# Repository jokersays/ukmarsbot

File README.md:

# update CW2025
## wall sensor
- LED (sichtbares Licht): TCLR5800 https://eu.mouser.com/ProductDetail/Vishay-Semiconductors/TLCR5800?qs=mUuSc%2Fu%252BFEmjc7YwQS0o5A%3D%3D&srsltid=AfmBOopzCn7n3C-wtkQbLPWO1j8fxE9Hj8DcGLDCGrcggpLkpXWju-RC
- Phototransistor: BPW96B https://www.mouser.de/ProductDetail/Vishay-Semiconductors/BPW96B?qs=%2Fjqivxn91cdilznm00Ncpg%3D%3D&utm_id=10065984414&utm_source=google&utm_medium=cpc&utm_marketing_tactic=emeacorp&gad_source=5&gad_campaignid=10065984414&gclid=EAIaIQobChMIq9jEloT5jgMVpy0GAB1_qAhfEAAYAiAAEgKWzvD_BwE

## motor
- N20 Gear Motor mit Encoder, 6V, 20:1 / ~1000 RPM (oder 750 RPM) AliExpress?

## capacitor
- 470uF 10V 6.3mm, <12mm h, radial 2.5
- 330uF 10V radial 2.5
--> mouser

# ukmarsbot

__A simple beginner's multi purpose robot platform__

Using inexpensive, readily available materials, components and techniques, the UK Micromouse and Robotics Society (UKMARS) has created a basic robot design that can be used in a variety of common contests such as line following, wall following, drag race and mini-sumo.

## Contents

This repository is all about the robot itself. Software is provided in other UKMARS repositories. 

 - Software examples https://github.com/ukmars/ukmarsbot-examples
 - Full maze solving software: https://github.com/ukmars/ukmarsbot-mazerunner

The repository has a number of sections:

 - [__docs__](docs) contains miscellaneous documentation and datasheets. In there are some notes about design decisions and constraints, processor choice and configuration, and a bit about sensors.
 - [__ecad__](ecad) contains the design files for the various electronic modules that make up the robot. The original development was done with Eagle Version 7 since it was the last 'free' version of Eagle. More recent versions are likely to be developed in KiCad since it is free, unconstrained and multiplatform. You are only likely to need to look in here f you want to modify existing modules or create your own. Either Eagle or KiCad can be used for new development.
 - [__hardware__](hardware) holds subsections for the major parts that make up the robot - the main PCB and all the sensor boards. This is where you find the outputs from the ECAD tools. You don't need to know anything about Eagle or KiCad to use these outputs. For each module you should find a set of gerbers in a zip file so that you can easily order boards from your favourite supplier. Also present should be the schematics in PDF form, images of the finished boards and a parts list (BOM) to help you populate the board and select components. Note that many component choices are up to the builder and there are a number of options possible. Some or all of these elements may be missing or incomplete. Let us know of any shortcomings by raising [a new issue on github](https://github.com/ukmars/ukmarsbot/issues).
 - [__mechanical__](mechanical) contains a number of mechanical CAD files. These are most likely to be STL or STEP files  and are for components that can be 3D printed tohelp you make your robot. For example you will find motor mounts and brackets here.
 - [__renders__](renders) is a place where we keep generated images of the robot and some components. You can get an idea of how your finished robot may look as well as see some of the prototypes that led to the current design.
 - [__resources__](resources) is really a dump for stuff that does not fit in with the rest. At the tie of writing this is just a section about data logging.

## The Processor
Processor power is provided by the Arduino Nano board because it is very cheap and widely available. There is a huge range of sample code available for almost any purpose and support is easily found online. The Arduino software can be installed on any computer and is free.

A proposed pin usage for an Arduino Nano controller can be found in the [docs](docs) folder.

because the Arduino Nano is a popular processor module, there are many compatible or near-compatible alternative boards available. The processor module socket makes it possible to use some of these directly with only small modifications or, with a little more work you might fit almost any processor. Variants have already been built with STM32 processors and even a Raspberry Pi pico and Zero board.

## Bluetooth

Some alternative processors in the Arduino range already have Bluetooth and WiFi built in. If you stick with simpler options - like the Arduino Nano - there is a connector provided for you to attach one of the common HC05 or HC06 Bluetooth modules directly to the board to make a wireless serial connection. Circuitry on the board (V1.1 and later) allowyou to leave the BT module connected during programming. You can then use any serial terminal, including the Arduino terminal, to communicate with the robot over Bluetooth.

### Coding
The easiest language for starting coding with the Arduino, and the method most people use, is to create a  "Sketch" using the Arduino Integrated Development Environment (IDE). A "Sketch" comprises functions written with C/C++ statements and the Arduino IDE takes care of turning the sketch into a complete program and uploading it to the Arduino board. It can run on any of the major platforms: Windows, Mac and Linux enabling Sketch programs for the Arduino to be readily developed on any PC. The Arduino project has lots of examples and help available for creating code, as well as libraries of functions to carry out specific tasks.

The Arduino IDE requires software to be downloaded and installed on the development PC as well as drivers to enable the developed code to be downloaded using the USB cable onto the Arduino board. All of this software and drivers are free and easy to install as long as you have software install permissions on the PC.

There is also a recently introduced web based development environment, but as yet this does not support all Arduino models and platforms. and still requires various plug ins to be installed on the development PC to use it. Find out more here: https://www.arduino.cc/en/software

A very popular alternative to the Arduino IDE is PlatformIO which can be fully integrated into the excellent VSCode editor. A 'getting started' guide for this environment is available here: https://docs.platformio.org/en/latest/integration/ide/vscode.html

Alternative software environments are available and are identified at the end of this document.

### Hardware

The robot hardware is constrained by the various contest events to be within certain dimensional limits. That means that the basic chassis will be smaller than 100mm x 100mm although add-on sensors for individual events will increase the size. The robot is designed to be multipurpose so there is a core hardware setup that provides for a basic wheelchair drive of two motors, encoder feedback for individual motor speed and a minimal interface for user interaction. Components will be modular so that substitutions are easy and to provide the greatest flexibility. Builders are free to make whatever modifications suit their purpose. For example, larger or smaller motors and wheels may be used and a variety of sensor options are possible.

### Power Supply

For most purposes, the power supply for the robot will need to be compact, readily available and easy to recharge. Non rechargeable batteries are not economically viable for robot experiment and are, in any case, less environmentally friendly. Safety is a concern and so Lithium Polymer cells are only recommended when part of a regulated and protected pack. Perhaps the most common small battery is the rechargeable PP3 sized pack running at 8.4 Volts or 9 Volts. Rechargeable cells and their chargers can be purchased at supermarkets and online suppliers. More confident, or adventurous builders may install whatever power supply suits them.

### Motors

While there is endless variety in small DC electric motors, the N20-based gearmotors are excellent value for money and can be purchased in a huge range of performance characteristics. An example can be found here: [Pimoroni 20:1 gearmotor](https://shop.pimoroni.com/products/micro-metal-gearmotor-extended-back-shaft?variant=32587847050). The common dimensions make it easy to swap motors without changing the mechanical design of the robot. Versions are available with built-in encoders allowing for more accurate control of speed and greater precision in movement of the robot. Normally these would be used in any robot. The drivers for these motors are available on small circuit board modules that can easily be connected with the Arduino Nano.

### Materials

It will be possible to build the robot using parts that are commercially readily available and specialist materials will not be required. Access to basic hand tools and soldering equipment will be necessary.

It is likely that some builders will have some access to a 3D printer or a laser cutter or both and the open design of the robot with upgrade paths will allow advanced builders to utilize these tools to create higher performing robots.

### Software

The two software repositories mentioned above provide a fairly complete set of examples and code for almost every aspect of programming for the UKMARSBOT platform. Many of the techniques and examples will also be directly applicable to other mobile robot projects.

If the Arduino IDE is not for you, then there are other programming choices to suit you. (__None of these have been tried by UKMARS__)

* FlashForth http://flashforth.com/ is a Forth stamp system implemented on the Microchip 8-bit PIC18F and 16-bit PIC24, 30, 33 and the Atmel Atmega microcontroller families. See also https://playground.arduino.cc/CommonTopics/ForthOnArduino/ for other options relating to Forth.

* For Basic users there appear to be fewer options. One of these is Great Cow basic http://gcbasic.sourceforge.net/Typesetter/index.php/Home. _"The  Great Cow BASIC suite is robust and fully functional compiler and assembler.   Using Great Cow BASIC is the fastest method to program a Microchip PIC or Atmel AVR 8-bit microcontroller for those just starting and the professional user."_  The host software is cross platform and there is a graphical editor as well as a more traditional IDE.

* Some users may prefer a visual programming environment similar to Scratch. Several of these are available and more information may be found here [Sparkfun Alternative Arduino Interfaces](https://learn.sparkfun.com/tutorials/alternative-arduino-interfaces/all).

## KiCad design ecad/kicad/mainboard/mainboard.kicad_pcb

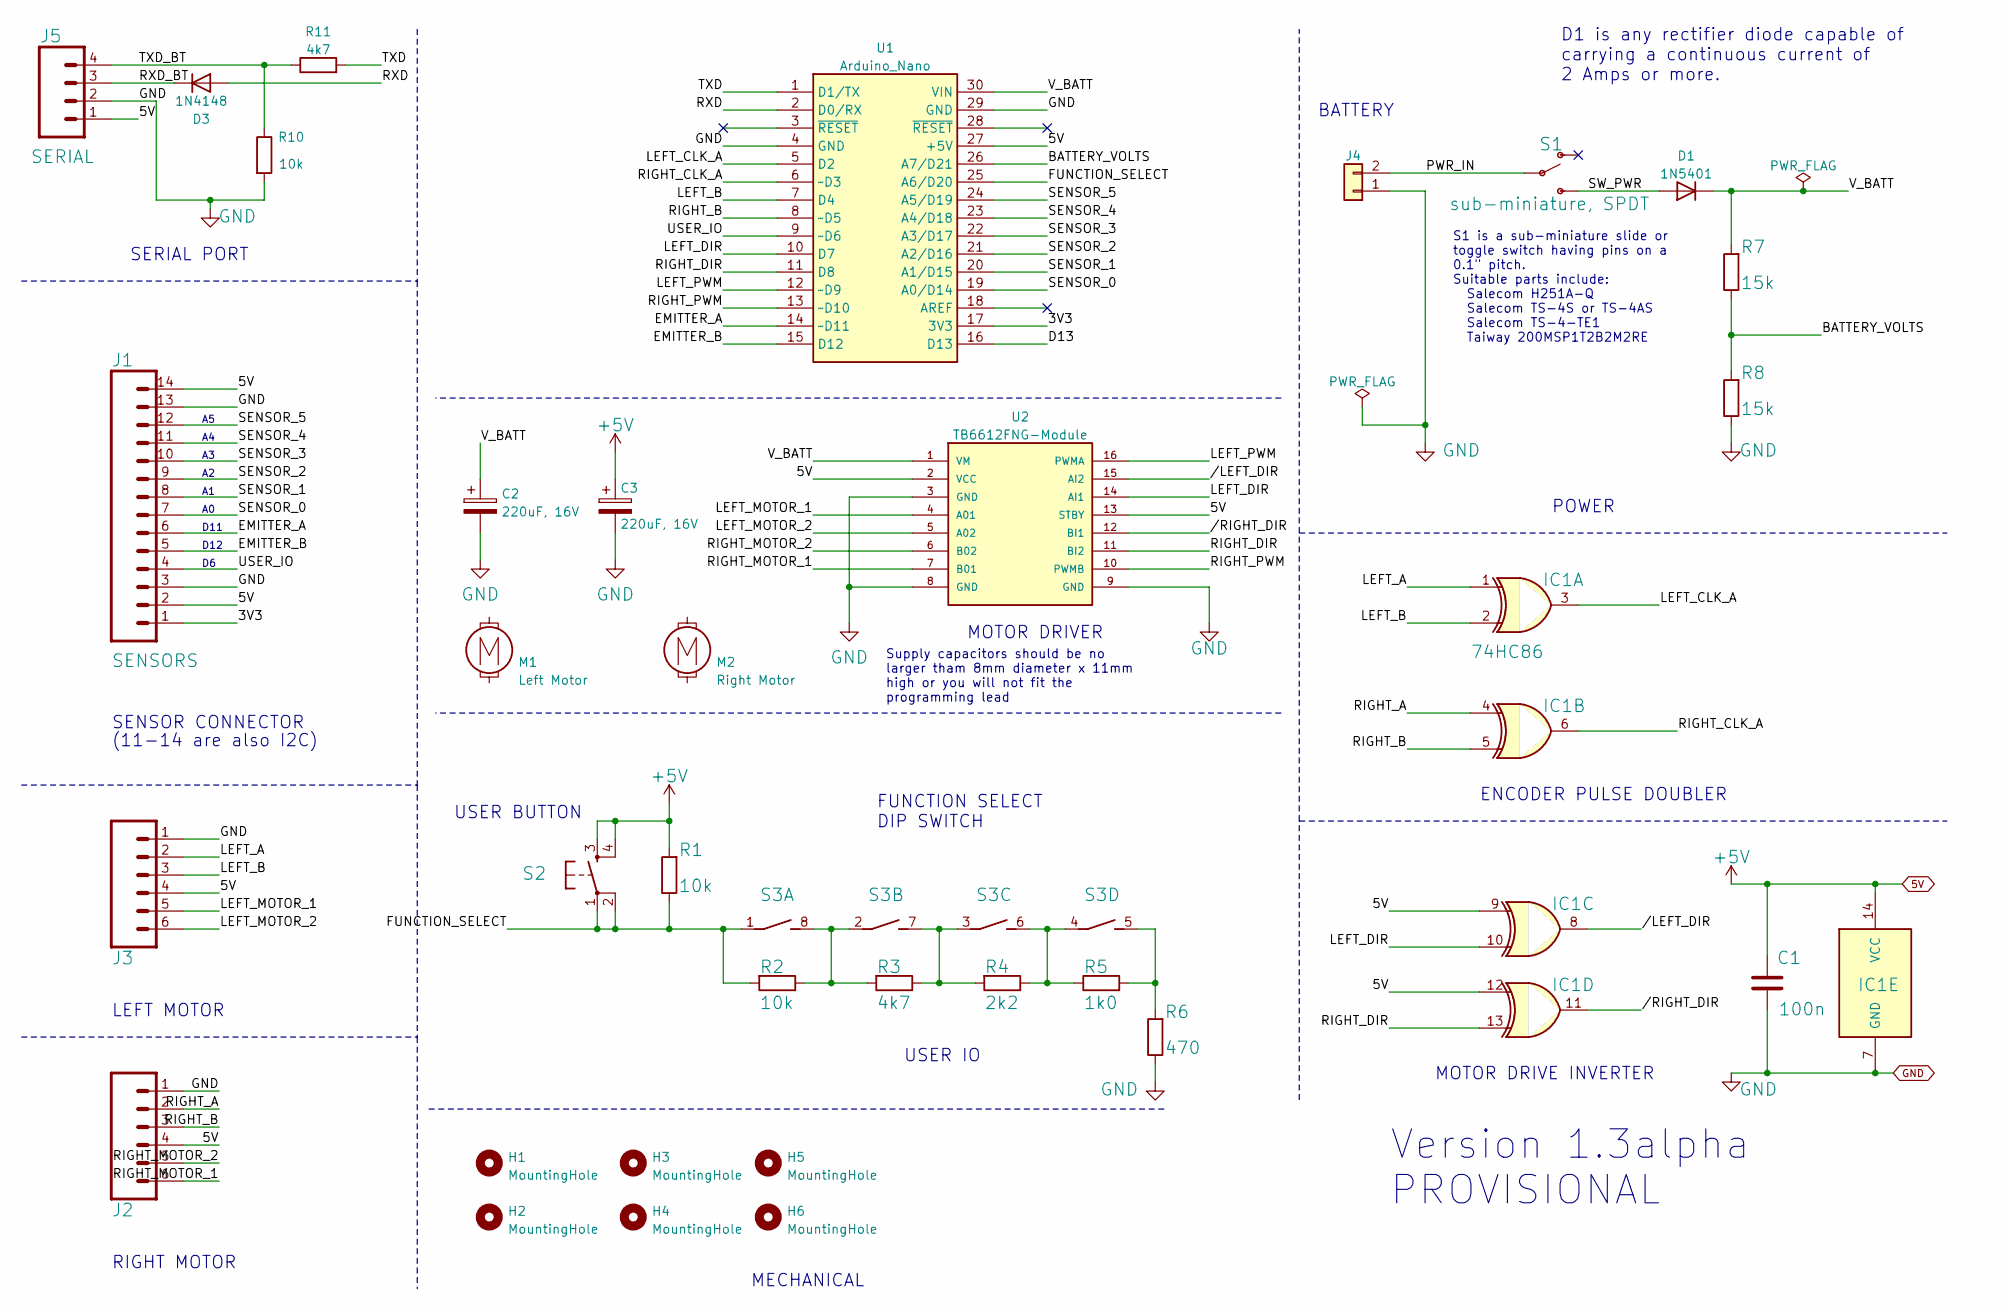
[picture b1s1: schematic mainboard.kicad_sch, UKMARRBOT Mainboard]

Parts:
C1: 100n; C_Rect_L4.6mm_W2.0mm_P2.50mm_MKS02_FKP02
C2, C3: 220uF, 16V; CP_Elec_8x10
D1: 1N5401; D_DO-201AD_P15.24mm_Horizontal
D3: 1N4148; D_DO-35_SOD27_P7.62mm_Horizontal
H1, H2, H3, H4, H5, H6: MountingHole; MountingHole_3.2mm_M3_clearance
IC1: 74HC86; DIP-14_W7.62mm_LongPads
J1: SENSORS; 1X14_LOCK_LONGPADS
J2, J3: CONN_06SILK_FEMALE_PTH; 1X06_LOCK_LONGPADS
J4: POWER; Molex_KK-254_AE-6410-02A_1x02_P2.54mm_Vertical
J5: SERIAL; 1X04_LOCK_LONGPADS
M1: Left Motor; MINI-METAL-GEARMOTOR-WITH-BRACKET
M2: Right Motor; MINI-METAL-GEARMOTOR-WITH-BRACKET
R1, R2, R10: 10k; R_Axial_DIN0207_L6.3mm_D2.5mm_P7.62mm_BIGPAD
R3, R11: 4k7; R_Axial_DIN0207_L6.3mm_D2.5mm_P7.62mm_BIGPAD
R4: 2k2; R_Axial_DIN0207_L6.3mm_D2.5mm_P7.62mm_BIGPAD
R5: 1k0; R_Axial_DIN0207_L6.3mm_D2.5mm_P7.62mm_BIGPAD
R6: 470; R_Axial_DIN0207_L6.3mm_D2.5mm_P7.62mm_BIGPAD
R7, R8: 15k; R_Axial_DIN0207_L6.3mm_D2.5mm_P7.62mm_BIGPAD
S1: sub-miniature, SPDT; SW_MINI-SPDT-SW
S2: BUTTON; TACTILE_SWITCH_PTH_6.0MM
S3: DIP-SW; SW_DIP_SPSTx04_Slide_6.7x11.72mm_W7.62mm_P2.54mm_LowProfile
U1: Arduino_Nano
U2: TB6612FNG-Module; TB6612FNG-module; PARTREV 11-13-17

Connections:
5V: C1.1, C3.1, IC1.9, IC1.12, IC1.14 (VCC), J1.2, J1.14, J2.4, J3.4, J5.1, R1.2, S2.3, S2.4, U1.27 (+5V), U2.2 (VCC), U2.13 (STBY)
/3V3: J1.1, U1.17 (3V3)
/BATTERY_VOLTS: R7.1, R8.2, U1.26 (A7/D21)
/D13: U1.16 (D13)
/EMITTER_A: J1.6, U1.14 (~D11)
/EMITTER_B: J1.5, U1.15 (D12)
/FUNCTION_SELECT: R1.1, R2.2, S2.1, S2.2, S3.1, U1.25 (A6/D20)
/LEFT_A: IC1.1, J3.2
/LEFT_B: IC1.2, J3.3, U1.7 (D4)
/LEFT_CLK_A: IC1.3, U1.5 (D2)
/LEFT_DIR: IC1.10, U1.10 (D7), U2.14 (AI1)
/LEFT_MOTOR_1: J3.5, U2.4 (A01)
/LEFT_MOTOR_2: J3.6, U2.5 (A02)
/LEFT_PWM: U1.12 (~D9), U2.16 (PWMA)
/PWR_IN: J4.2, S1.2
/RIGHT_A: IC1.4, J2.2
/RIGHT_B: IC1.5, J2.3, U1.8 (~D5)
/RIGHT_CLK_A: IC1.6, U1.6 (~D3)
/RIGHT_DIR: IC1.13, U1.11 (D8), U2.11 (BI2)
/RIGHT_MOTOR_1: J2.6, U2.7 (B01)
/RIGHT_MOTOR_2: J2.5, U2.6 (B02)
/RIGHT_PWM: U1.13 (~D10), U2.10 (PWMB)
/RXD: D3.2 (A), U1.2 (D0/RX)
/RXD_BT: D3.1 (K), J5.3
/SENSOR_0: J1.7, U1.19 (A0/D14)
/SENSOR_1: J1.8, U1.20 (A1/D15)
/SENSOR_2: J1.9, U1.21 (A2/D16)
/SENSOR_3: J1.10, U1.22 (A3/D17)
/SENSOR_4: J1.11, U1.23 (A4/D18)
/SENSOR_5: J1.12, U1.24 (A5/D19)
/SW_PWR: D1.2 (A), S1.3 (S)
/TXD: R11.2, U1.1 (D1/TX)
/TXD_BT: J5.4, R10.1, R11.1
/USER_IO: J1.4, U1.9 (~D6)
/V_BATT: C2.1, D1.1 (K), R7.2, U1.30 (VIN), U2.1 (VM)
//LEFT_DIR: IC1.8, U2.15 (AI2)
//RIGHT_DIR: IC1.11, U2.12 (BI1)
GND: C1.2, C2.2, C3.2, IC1.7 (GND), J1.3, J1.13, J2.1, J3.1, J4.1, J5.2, R6.1, R8.1, R10.2, U1.4 (GND), U1.29 (GND), U2.3 (GND), U2.8 (GND), U2.9 (GND)
unnamed: R2.1, R3.2, S3.2 (1), S3.8 (2)
unnamed: R3.1, R4.2, S3.3 (1), S3.7 (2)
unnamed: R4.1, R5.1, S3.4 (1), S3.6 (2)
unnamed: R5.2, R6.2, S3.5 (2)

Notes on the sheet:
MOTOR DRIVER
D1 is any rectifier diode capable of carrying a continuous current of 2 Amps or more.
USER IO
POWER
MOTOR DRIVE INVERTER
FUNCTION SELECT DIP SWITCH
Supply capacitors should be no larger tham 8mm diameter x 11mm high or you will not fit the programming lead
S1 is a sub-miniature slide or toggle switch having pins on a 0.1" pitch. Suitable parts include: Salecom H251A-Q Salecom TS-4S or TS-4AS Salecom TS-4-TE1 Taiway 200MSP1T2B2M2RE
RIGHT MOTOR
SERIAL PORT
SENSOR CONNECTOR
BATTERY
MECHANICAL
ENCODER PULSE DOUBLER
USER BUTTON
D11
Version 1.3alpha PROVISIONAL
LEFT MOTOR
(11-14 are also I2C)
D12

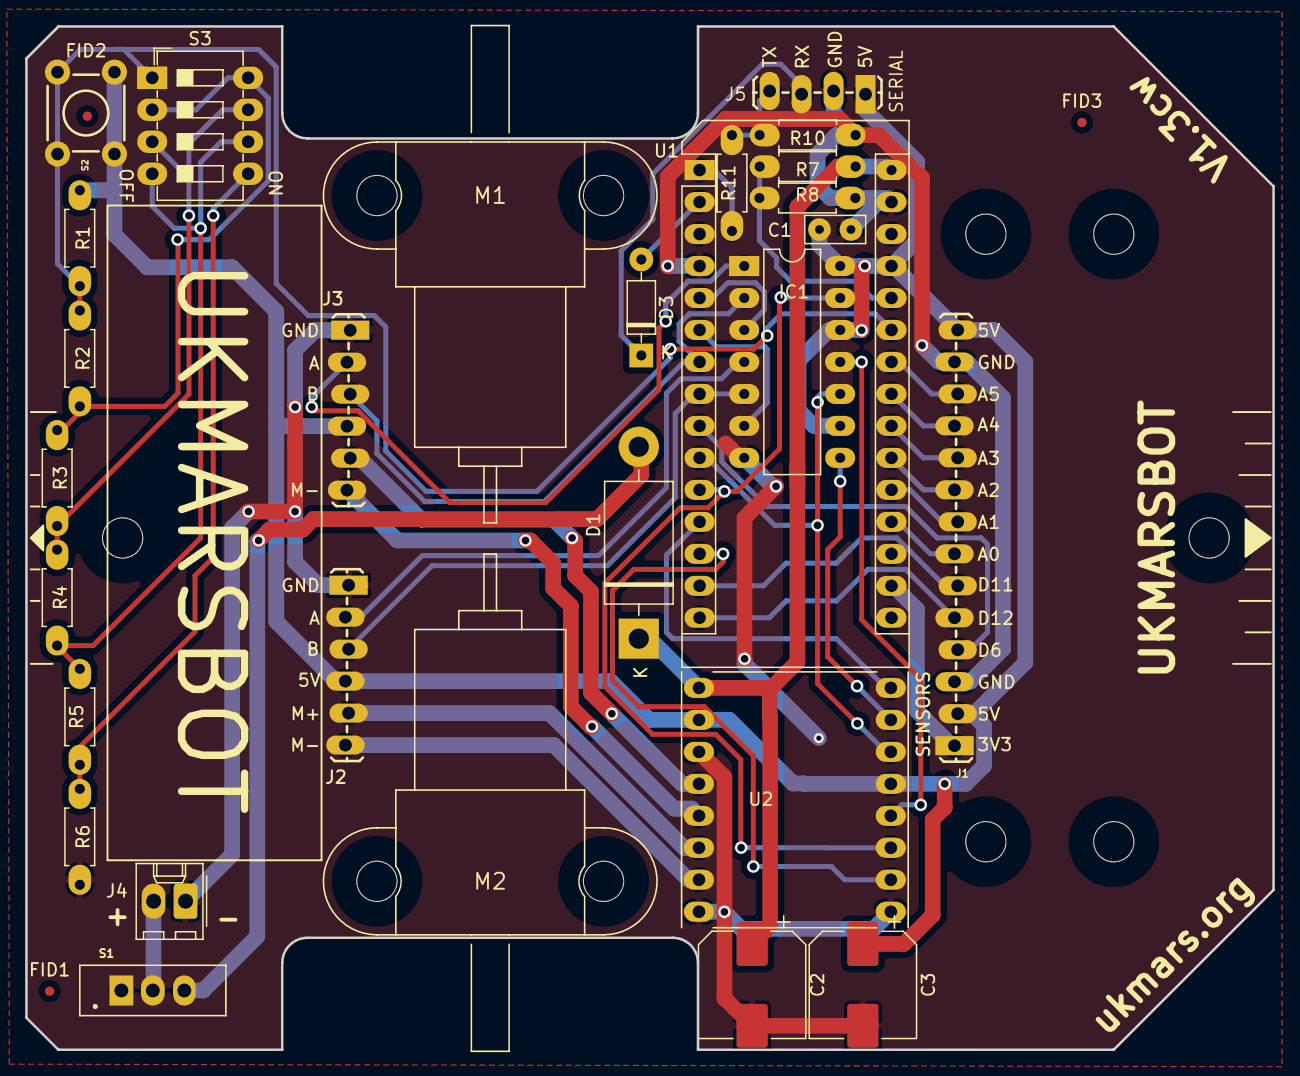
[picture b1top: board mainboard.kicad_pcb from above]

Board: 2 copper layers, 99.1 x 81.3 mm, 37 parts (0 on the bottom side), 41 nets.

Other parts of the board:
FID1, FID2, FID3: Fiducial_0.75mm_Mask1.5mm

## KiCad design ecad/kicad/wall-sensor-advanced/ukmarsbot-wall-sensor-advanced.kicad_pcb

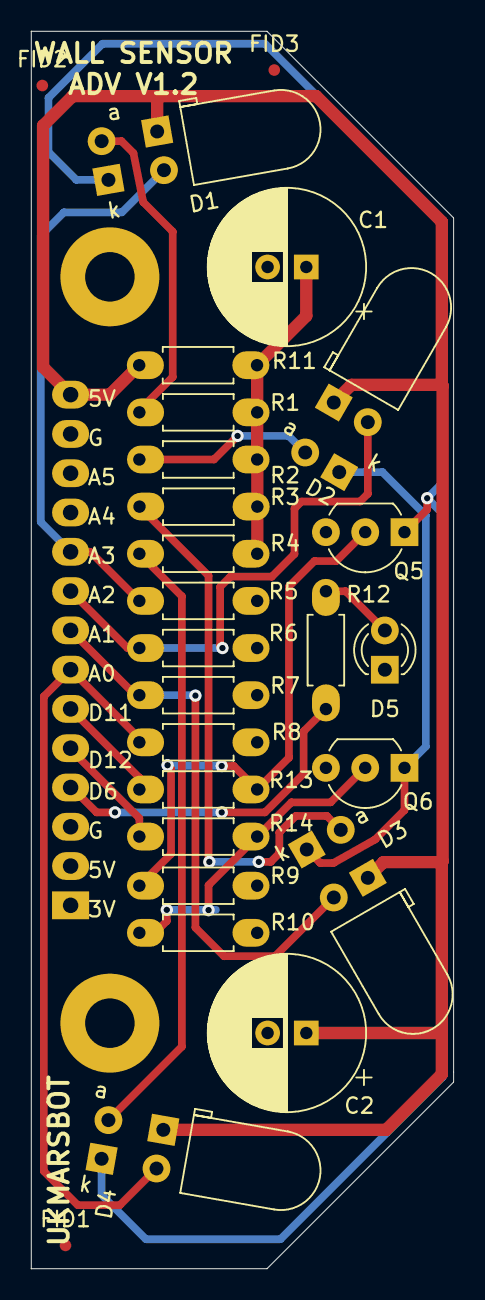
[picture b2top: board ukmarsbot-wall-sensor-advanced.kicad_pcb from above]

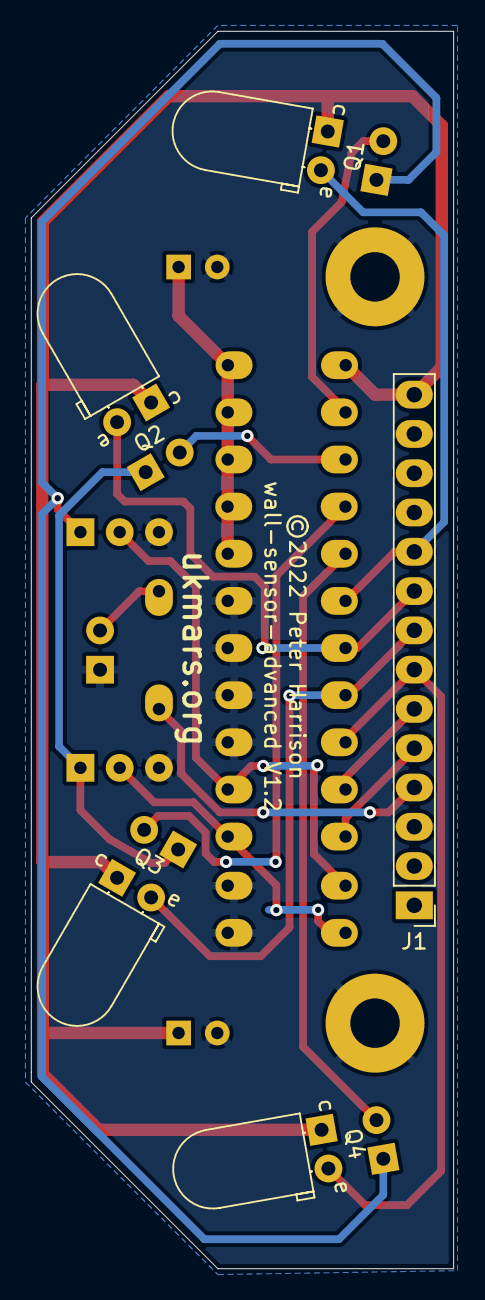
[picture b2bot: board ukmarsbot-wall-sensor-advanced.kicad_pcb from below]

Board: 2 copper layers, 27.3 x 80.0 mm, 33 parts (5 on the bottom side), 19 nets.

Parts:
C1, C2: 330uF, 16V; CP_Radial_D10.0mm_P2.50mm
D1, D2, D3, D4: SFH4545; LED_D5.0mm_Horizontal_O6.35mm_Z3.0mm
D5: LED; LED_D3.0mm
FID1, FID2, FID3: Fiducial_0.75mm_Mask1.5mm
H1, H2: 3.2mm; MountingHole_3.2mm_M3_Pad
J1: Conn_01x14; PinHeader_1x14_P2.54mm_Vertical_Longpads
Q1, Q2, Q3, Q4: TEFT4300; LED_D5.0mm_Horizontal_O1.27mm_Z3.0mm_IRGrey
Q5, Q6: BC337; TO-92_Inline_Wide_HandSolder
R1, R2, R3, R4: 10R; R_Axial_DIN0207_L6.3mm_D2.5mm_P7.62mm_BIGPAD
R5, R6, R7, R8: 1k8; R_Axial_DIN0207_L6.3mm_D2.5mm_P7.62mm_BIGPAD
R9, R10: 100k; R_Axial_DIN0207_L6.3mm_D2.5mm_P7.62mm_BIGPAD
R11: 33; R_Axial_DIN0207_L6.3mm_D2.5mm_P7.62mm_BIGPAD
R12: 1k0; R_Axial_DIN0207_L6.3mm_D2.5mm_P7.62mm_BIGPAD
R13, R14: 390R; R_Axial_DIN0207_L6.3mm_D2.5mm_P7.62mm_BIGPAD

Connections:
5V: C2.1, J1.14, Q1.1 (C), Q2.1 (C), Q3.1 (C), Q4.1 (C), R11.2
/DIA_COMMON: D2.1 (K), D3.1 (K), Q6.1 (C)
/FWD_COMMON: D1.1 (K), D4.1 (K), Q5.1 (C)
A0_RF: J1.7, Q4.2 (E), R8.1
A1_RD: J1.8, Q3.2 (E), R7.1
A2_LD: J1.9, Q2.2 (E), R6.1
A3_LF: J1.10, Q1.2 (E), R5.1
D6_LED: J1.4, R12.2
D11_FRONT: J1.6, R13.1
D12_DIAGONAL: J1.5, R14.1
GND: C1.2, C2.2, D5.1 (K), H1.1, H2.1, J1.3, J1.13, Q5.3 (E), Q6.3 (E), R5.2, R6.2, R7.2, R8.2, R9.2, R10.2
unnamed: D1.2 (A), R1.1
unnamed: D2.2 (A), R2.1
unnamed: D3.2 (A), R3.1
unnamed: D4.2 (A), R4.1
unnamed: D5.2 (A), R12.1
unnamed: Q5.2 (B), R9.1, R13.2
unnamed: Q6.2 (B), R10.1, R14.2
V_LED: C1.1, R1.2, R2.2, R3.2, R4.2, R11.1

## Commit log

2025-07-21 Zwischenstand: IBOM, Layout
2025-07-22 Zwischenstand Layout
2025-07-22 changed pads to connected layer only
2025-07-22 changed all pads to connected layer only
2025-07-22 layout
2025-07-22 lock clean
2025-07-22 Layout fertig (fast)
2025-07-23 final layout 1.3cw
2025-07-23 ibom neu
2025-07-25 added missing via
2025-08-07 Parts

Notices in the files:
ecad/kicad/wall-sensor-advanced/ukmarsbot-wall-sensor-advanced.kicad_pcb:
©2022 Peter Harrison
